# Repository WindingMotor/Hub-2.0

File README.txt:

:+#@@@@@@##:                                                          ::
   :#@@@@###@@@@@@+                                                    ++#+::
  :@@#:       +@@@@+                                                   +@:+#+#+::  :+@@@@#
  @@+  :@@@@:  #@@@# +@@@@@@:  :@@@@@  #@@@@+                    ~~~  :++#@###+::::++@@@@#
  @@   @@@@#  :@@@@  @@@@@@@+  +@@@@@ :@@@@@:             ~~~~ ~~~~~~++  #@+  :+@:::+@@@@#~
  :@  +@@@@##@@@#+  @@@@:@@@#  #@@@@@+@@@@@@            :~~~:::::++#++###@@:###+#+   +##@#  ~~~~
    : @@@@#+@@@@@: +@@@+:@@@#  @@@@@@@@@@@@@      ::::@@+ :+#+::::+#+:::+++:::++##+::  +##~~~~ ~~~
     #@@@@  +@@@@  @@@@@@@@@@ :@@@+#@@#+@@@+     ~@@@@+  +#@@@#@+ ##++##:#@######@@@@ :@#++~~~
    :@@@@:  @@@@+ @@@@+++@@@@ +@@@+#@@##@@@:    ~#@##::+##+###@@@ ++:#:@@+@@@@@@@@@@@+ ++++~~~~
    :::::   ::::  ::::   :::::   :::::        :##+::##+:+#:+#@@@#:++@++##@@@@####@@@@+:++~~~
                              #@@@@@@@@@@@@:
                            +@@@#:    :#@@@@+
        ~~: :+++:   ##:    :@@+  :++++  +@@@@  :+:::::     :++++::  +++  ::::  :+++    :+++++:
      ~~~:#@@##@@@#+#@@+   #@+  :@@@@+  +@@@@ :@@@@@@@   #@@@@@@@# #@@@: @@@@# #@@@  +@@@@@@@@:
     ~~~+@@#+: :@@@@@@@@:  :@:  #@@@@ :#@@@#  @@@@@@@@  #@@@@@@@@: @@@@ :@@@@@+@@@# +@@@@#####
     ~~~#@:@@@:@@@@@@@@@@:  :+ :@@@@@@@@@@+  #@@@ #@@@ :@@@@      :@@@# #@@@@@@@@@+ @@@@: ::::
    ~~~~+@::+#:+@@@@@@@@@#     @@@@+  @@@@# :@@@@#@@@@ +@@@@:  :: +@@@+ @@@@+@@@@@: @@@#  @@@#
     ~~~~~:       :++++: :    #@@@@  +@@@@  @@@@@@@@@@: @@@@@@@@+ @@@@  @@@# #@@@@  @@@@##@@@:
        ~~~++++++++####+++    ####:  ####+ +@@@+  +@@@+ :#@@@@@@  @@@# :@#@:  @@@#   +#@@@@##

VCU Ram Racing Distribution Hub 2.0
===================================

The Distribution Hub 2.0 is the central power and signal board for VCU-04.
It sits between the M130 ECU and the rest of the wiring harness, switching power to the car's loads
and routing sensor, dash, and communication signals through a single board.

Contributors
------------

  Isaac Subudhi     Team Lead, and all sheets.
  Brandon Estrada   Low Power Relays
  Will Schindler    Status Indicators
  Jessie Vargas     ECU Interface (assist)

Documentation
-------------

A PDF and PNG images of every schematic sheet are in documentation/images.
They are regenerated automatically on each push to main.

Project Files
-------------

Open Hub-2.0.kicad_pro in KiCad. Schematics and the PCB are at the project root.
EasyEDA libraries and 3D models are included with the project.

Simulation
----------

Save and refill the PCB before launching KiPI.

  Linux:    ./simulation/run.sh
  Windows:  simulation\run.bat

Edit simulation/config.json for currents and model settings.
Comparison presets are in simulation/cases; tests are in simulation/tests.
See simulation/README.md for instructions and model assumptions.

Generated runs, downloaded tools, local environments, backups, and editor
history are ignored by Git. Keep board files, libraries, and configs tracked.

Prism Collaboration
-------------------

Project: https://ramracing-prism.larkspurindustries.com/project/prj_d483e5fd3cd7

.prism.json maps this repository's schematic, PCB, README, and design outputs
for Prism, including when browsing a specific Git revision.

The Assembly Assistant reads Design-Outputs/ibom.html. After changing the PCB,
regenerate it on Linux with KiCad installed:

  ./scripts/generate-assembly.sh

The script downloads a pinned version of InteractiveHtmlBom into a temporary
directory and generates a self-contained assembly page. Commit the updated
HTML together with the PCB so both describe the same revision. These assembly
outputs assist placement; they do not replace electrical/design review.

See documentation/PRISM.md for revision reviews, automatic assembly/docs updates,
KiCad Remote Symbols, simulation provenance and report sharing, and Release Studio.

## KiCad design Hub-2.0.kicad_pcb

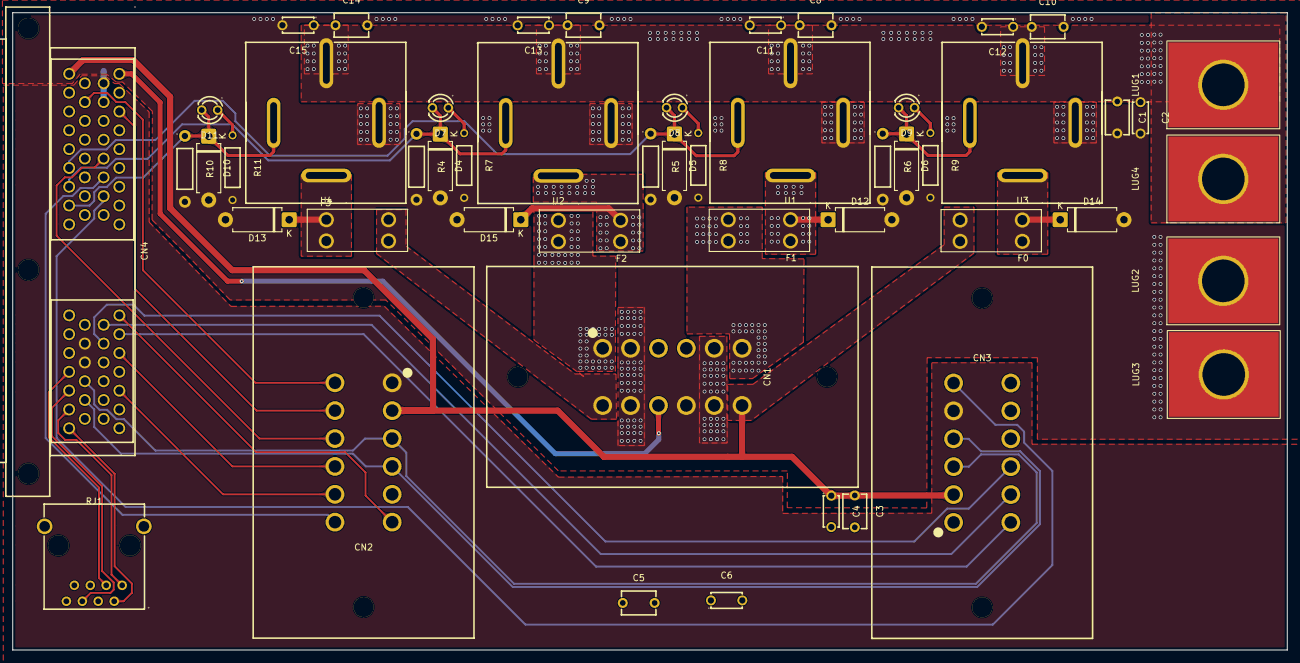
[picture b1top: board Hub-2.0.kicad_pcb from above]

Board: 6 copper layers, 203.2 x 101.6 mm, 51 parts (0 on the bottom side), 37 nets.

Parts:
C1, C3, C5, C8, C9, C10, C14: 10u; CAP-TH_L5.5-W3.8-P5.08-D0.5
C2, C4, C6, C11, C12, C13, C15: 100n; CAP-TH_L5.0-W2.5-P5.00-D1.0
CN1, CN2, CN3: DT15-12PA; CONN-TH_DT15-12PA
CN4: 6437288-3-MODIFIED; DSUB-60P_SUPERSEAL
D4, D5, D6, D10, D12, D13, D14, D15: 1N5399; D_DO-15_P10.16mm_Horizontal
D7, D8, D9, D11: LED; LED-TH_BD3.0-P2.54-FD_YELLOW
F0, F1, F2, F3: Fuse; FUSE_3568
LUG1: +12V_BATT_LUG; 1_4_Lug
LUG2: GND_LUG; 1_4_Lug
LUG3: GND_ENGINE_CHASSIS_LUG; 1_4_Lug
LUG4: +12V_STARTER_RELAY; 1_4_Lug
R4, R5, R6, R10: 10k; RES-TH_BD2.5-L6.5-P10.50-D0.6
R7, R8, R9, R11: 660; RES-TH_BD2.4-L6.3-P10.30-D0.6
RJ1: R-RJ45S08P-B000; RJ45-TH_R-RJ45S08P-B000
U1, U2, U3, U4: YQ506-S-112 DM; RELAY-TH_YQ506-S-112DM

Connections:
+12V_BATT: C1.1, C2.1, C8.1, C9.1, C10.1, C11.1, C12.1, C13.1, C14.1, C15.1, LUG1.1 (Pin_1_1), LUG4.1 (Pin_1_1), U1.30, U2.30, U3.30, U4.30
+12V_MAIN: C3.1, C4.1, C5.1, C6.1, CN1.7, CN2.2, CN3.2, CN4.45 (A26_BAT_POS), F0.2
/LOW_POWER_RELAYS/PWR_FUEL_PUMP_BEFORE_FUSE: D12.1 (K), F1.1, U1.87
/LOW_POWER_RELAYS/PWR_LIGHTS_BEFORE_FUSE: D13.1 (K), F3.1, U4.87
/LOW_POWER_RELAYS/PWR_MAIN_BEFORE_FUSE: D14.1 (K), F0.1, U3.87
/LOW_POWER_RELAYS/PWR_RADIATOR_BEFORE_FUSE: D15.1 (K), F2.1, U2.87
BTN_DASH_ONE: CN3.11, CN4.25 (B08_UDIG3)
BTN_DASH_STARTER: CN3.12, CN4.11 (B02_UDIG2)
BTN_DASH_TWO: CN3.10, CN4.26 (B09_UDIG4)
COMM_CAN_HIGH: CN2.3, CN3.3, CN4.42 (B17_CAN_HI)
COMM_CAN_LOW: CN2.4, CN3.4, CN4.43 (B18_CAN_LO)
COMM_ETH_GW_TX+: CN4.57 (B23_ETH_TX+), RJ1.3
COMM_ETH_G_TX-: CN4.58 (B24_ETH_TX-), RJ1.6
COMM_ETH_OW_RX+: CN4.59 (B25_ETH_RX+), RJ1.1
COMM_ETH_O_RX-: CN4.60 (B26_ETH_RX-), RJ1.2
EN_HS_BRAKE_LIGHT: CN1.10, CN4.1 (A01_OUT_HB2)
EN_HS_FUEL_PUMP: CN4.50 (A31_OUT_HB3), D5.1 (K), D8.2 (A), R5.1, U1.85
EN_HS_LIGHTS: CN4.52 (A33_OUT_HB5), D10.1 (K), D11.2 (A), R10.1, U4.85
EN_HS_RADIATOR: CN4.51 (A32_OUT_HB4), D4.1 (K), D7.2 (A), R4.1, U2.85
GND: C1.2, C2.2, C3.2, C4.2, C5.2, C6.2, C8.2, C9.2, C10.2, C11.2, C12.2, C13.2, C14.2, C15.2, CN1.2, CN1.5, CN1.8, CN1.9, CN1.11, CN3.1, CN4.17 (A10_BAT_NEG1), CN4.18 (A11_BAT_NEG2), D4.2 (A), D5.2 (A), D6.2 (A), D10.2 (A), D12.2 (A), D13.2 (A), D14.2 (A), D15.2 (A), LUG2.1 (Pin_1_1), LUG3.1 (Pin_1_1), R4.2, R5.2, R6.2, R7.2, R8.2, R9.2, R10.2, R11.2, U1.86, U2.86, U3.86, U4.86
GNDS: CN2.1, CN3.5, CN4.40 (B15_SEN_0V_A), CN4.41 (B16_SEN_0V_B)
unnamed: D7.1 (K), R7.1
unnamed: D8.1 (K), R8.1
unnamed: D9.1 (K), R9.1
unnamed: D11.1 (K), R11.1
PWR_EN_MAIN: D6.1 (K), D9.2 (A), R6.1, U3.85
PWR_FUEL_PUMP: CN1.6, F1.2
PWR_LIGHTS: CN1.12, F3.2
PWR_RADIATOR: CN1.1, F2.2
SIG_BRAKE_F: CN3.6, CN4.23 (A16_AV3)
SIG_CLN: CN2.9, CN4.12 (B03_AT1)
SIG_IAT: CN2.8, CN4.14 (B05_AT3)
SIG_IGN: CN2.11, CN4.3 (A03_IGN_LS1)
SIG_INJ: CN2.12, CN4.32 (A19_INJ_PH1)
SIG_MAP: CN2.7, CN4.22 (A15_AV2)
SIG_RPM: CN2.6, CN4.10 (B01_UDIG1)
SIG_TPS: CN2.10, CN4.21 (A14_AV1)
